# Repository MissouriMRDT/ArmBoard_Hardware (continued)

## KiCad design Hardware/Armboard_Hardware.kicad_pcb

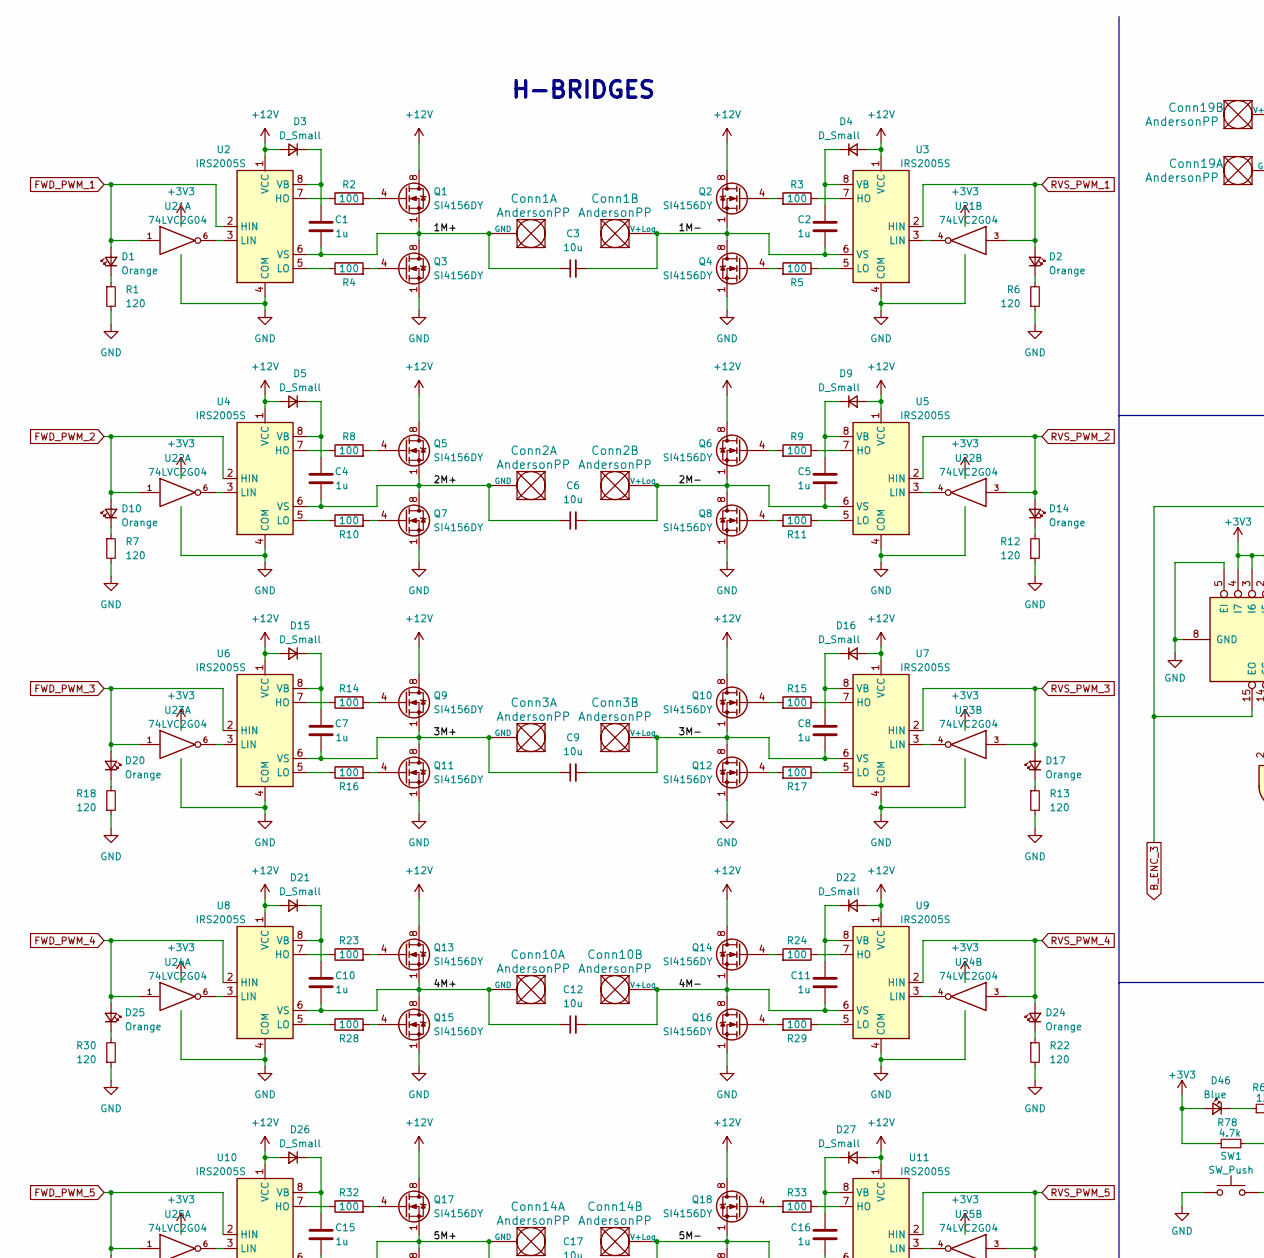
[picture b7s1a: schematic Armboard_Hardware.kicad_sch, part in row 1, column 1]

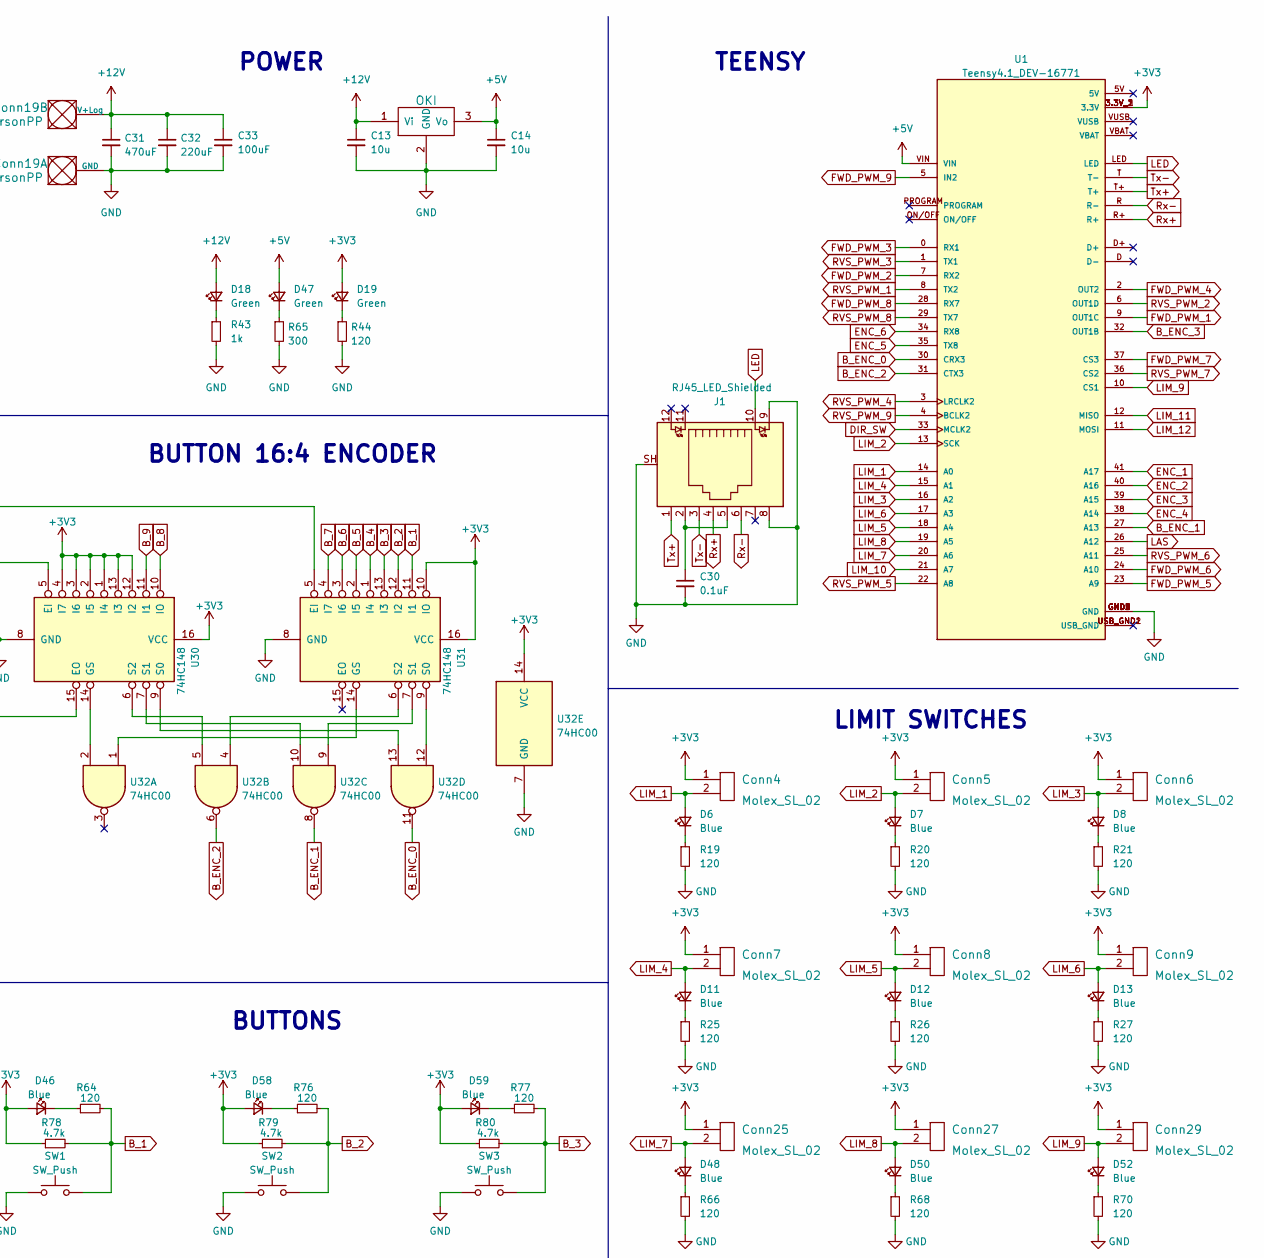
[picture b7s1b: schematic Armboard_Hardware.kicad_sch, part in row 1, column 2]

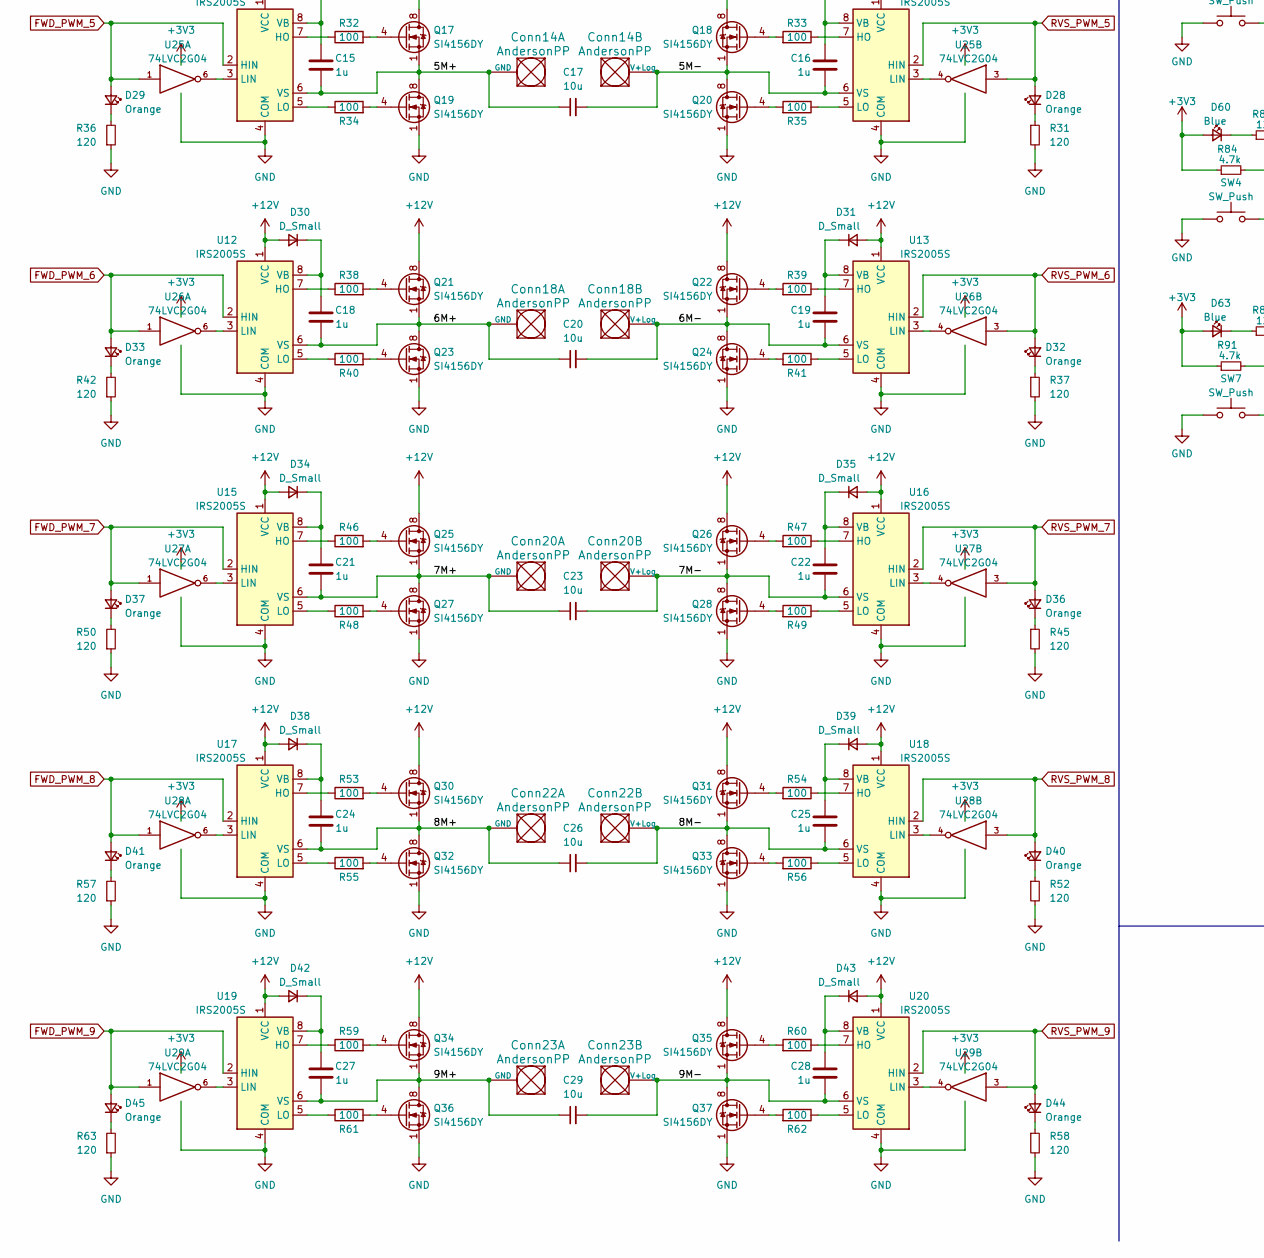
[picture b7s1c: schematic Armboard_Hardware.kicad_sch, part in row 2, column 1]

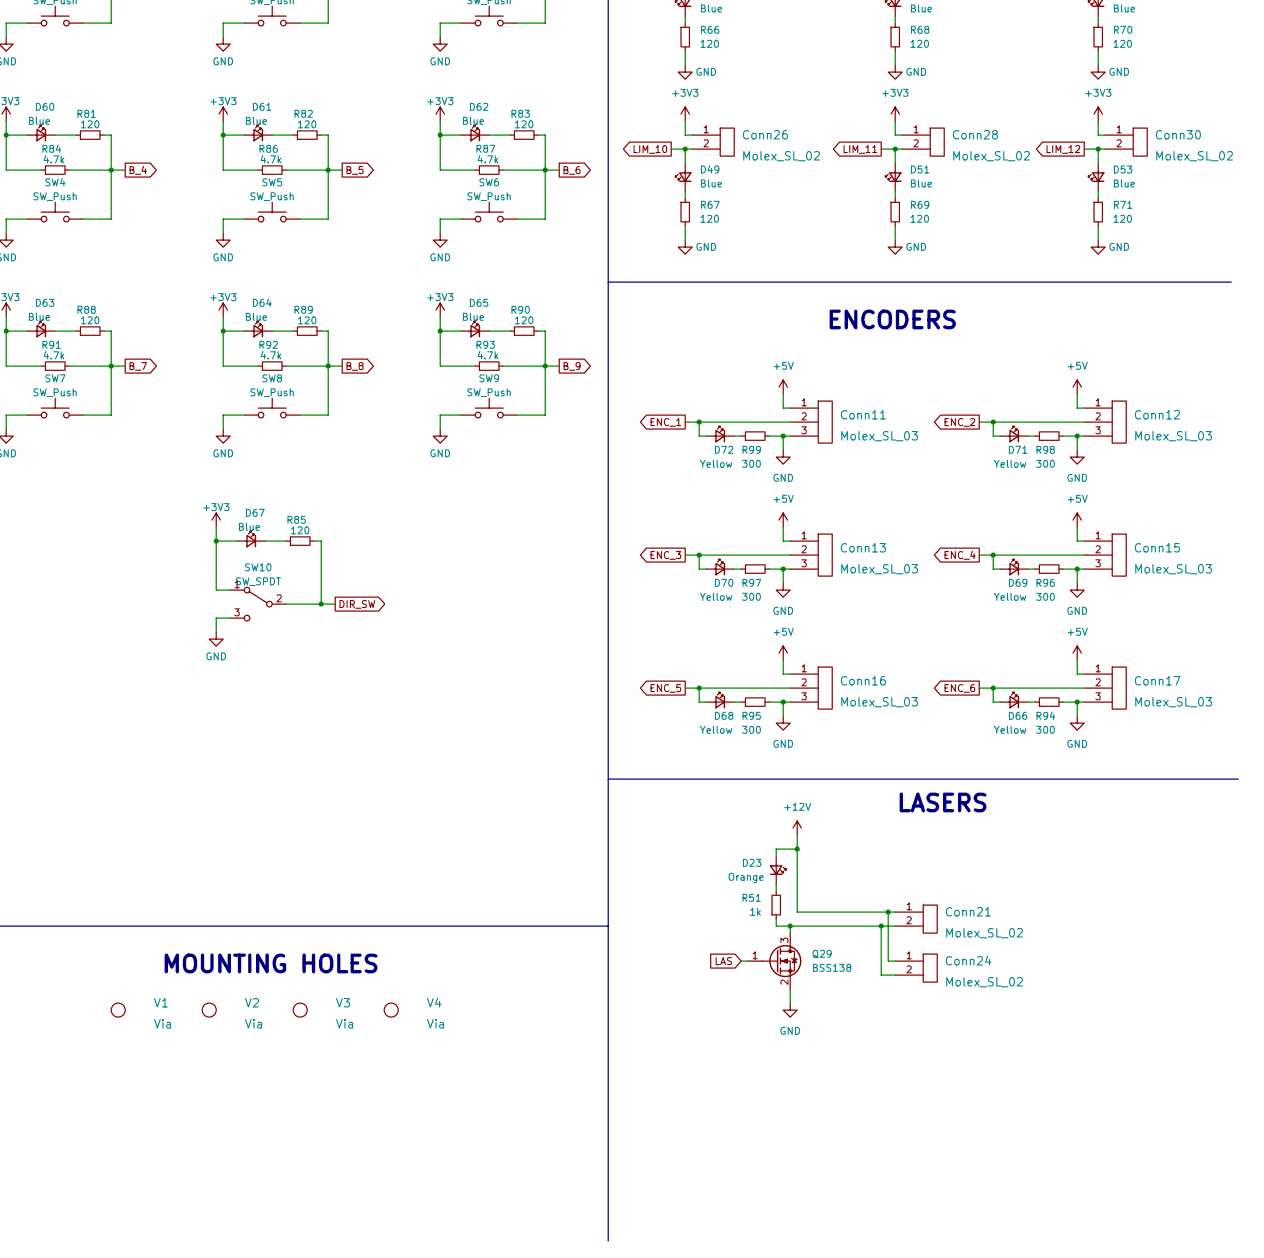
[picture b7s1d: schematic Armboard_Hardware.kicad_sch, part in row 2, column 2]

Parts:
C1, C2, C4, C5, C7, C8, C10, C11, C15, C16, C18, C19, C21, C22, C24, C25, C27, C28: 1u; C_0603_1608Metric
C3, C6, C9, C12, C13, C14, C17, C20, C23, C26, C29: 10u; C_0603_1608Metric
C30: 0.1uF; C_0603_1608Metric
C31: 470uF; CP_Radial_D10.0mm_P2.50mm
C32: 220uF; CP_Radial_D6.3mm_P2.50mm
C33: 100uF; CP_Radial_D6.3mm_P2.50mm
Conn1, Conn2, Conn3, Conn10, Conn14, Conn18, Conn19, Conn20, Conn22, Conn23: AndersonPP; Square_Anderson_2_H_Side_By_Side
Conn4, Conn5, Conn6, Conn7, Conn8, Conn9, Conn21, Conn24, Conn25, Conn26, Conn27, Conn28, Conn29, Conn30: Molex_SL_02; Molex_SL_171971-0002_1x02_P2.54mm_Vertical
Conn11, Conn12, Conn13, Conn15, Conn16, Conn17: Molex_SL_03; Molex_SL_171971-0003_1x03_P2.54mm_Vertical
D1, D2, D10, D14, D17, D20, D23, D24, D25, D28, D29, D32, D33, D36, D37, D40, D41, D44, D45: Orange; LED_0603_1608Metric_Pad1.05x0.95mm_HandSolder
D3, D4, D5, D9, D15, D16, D21, D22, D26, D27, D30, D31, D34, D35, D38, D39, D42, D43: D_Small; LED_0603_1608Metric_Pad1.05x0.95mm_HandSolder
D6, D7, D8, D11, D12, D13, D46, D48, D49, D50, D51, D52, D53, D58, D59, D60, D61, D62, D63, D64, D65, D67: Blue; LED_0603_1608Metric_Pad1.05x0.95mm_HandSolder
D18, D19, D47: Green; LED_0603_1608Metric_Pad1.05x0.95mm_HandSolder
D66, D68, D69, D70, D71, D72: Yellow; LED_0603_1608Metric_Pad1.05x0.95mm_HandSolder
J1: RJ45_LED_Shielded; RJ45_Teensy
Q1, Q2, Q3, Q4, Q5, Q6, Q7, Q8, Q9, Q10, Q11, Q12, Q13, Q14, Q15, Q16, Q17, Q18, Q19, Q20, Q21, Q22, Q23, Q24, Q25, Q26, Q27, Q28, Q30, Q31, Q32, Q33, Q34, Q35, Q36, Q37: SI4156DY; SOIC-8_3.9x4.9mm_P1.27mm
Q29: BSS138; SOT-23
R1, R6, R7, R12, R13, R18, R19, R20, R21, R22, R25, R26, R27, R30, R31, R36, R37, R42, R44, R45, R50, R52, R57, R58, R63, R64, R66, R67, R68, R69, R70, R71, R76, R77, R81, R82, R83, R85, R88, R89, R90: 120; R_0603_1608Metric_Pad0.98x0.95mm_HandSolder
R2, R3, R4, R5, R8, R9, R10, R11, R14, R15, R16, R17, R23, R24, R28, R29, R32, R33, R34, R35, R38, R39, R40, R41, R46, R47, R48, R49, R53, R54, R55, R56, R59, R60, R61, R62: 100; R_0603_1608Metric_Pad0.98x0.95mm_HandSolder
R43, R51: 1k; R_0603_1608Metric_Pad0.98x0.95mm_HandSolder
R65, R94, R95, R96, R97, R98, R99: 300; R_0603_1608Metric_Pad0.98x0.95mm_HandSolder
R78, R79, R80, R84, R86, R87, R91, R92, R93: 4.7k; R_0603_1608Metric_Pad0.98x0.95mm_HandSolder
SW1, SW2, SW3, SW4, SW5, SW6, SW7, SW8, SW9: SW_Push; SW_SPST_TL3305A
SW10: SW_SPDT; SW_Slide_1P2T_CK_OS102011MS2Q
U1: Teensy4.1_DEV-16771; Teensy_4_1_Ethernet; PARTREV 4.1
U2, U3, U4, U5, U6, U7, U8, U9, U10, U11, U12, U13, U15, U16, U17, U18, U19, U20: IRS2005S; SOIC-8_3.9x4.9mm_P1.27mm
U14: OKI; OKI_Horizontal
U21, U22, U23, U24, U25, U26, U27, U28, U29: 74LVC2G04; SOT-23-6_Handsoldering
U30, U31: 74HC148; SOIC-16_4.55x10.3mm_P1.27mm
U32: 74HC00; SO-14_5.3x10.2mm_P1.27mm
V1, V2, V3, V4: Via; 4_40_Hole_Corner

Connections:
+3V3: Conn4.1, Conn5.1, Conn6.1, Conn7.1, Conn8.1, Conn9.1, Conn25.1, Conn26.1, Conn27.1, Conn28.1, Conn29.1, Conn30.1, D19.2 (A), D46.2 (A), D58.2 (A), D59.2 (A), D60.2 (A), D61.2 (A), D62.2 (A), D63.2 (A), D64.2 (A), D65.2 (A), D67.2 (A), R78.1, R79.1, R80.1, R84.1, R86.1, R87.1, R91.1, R92.1, R93.1, SW10.1 (A), U1.3.3V_1 (3.3V), U1.3.3V_2 (3.3V), U1.3.3V_3 (3.3V), U21.5 (VCC), U22.5 (VCC), U23.5 (VCC), U24.5 (VCC), U25.5 (VCC), U26.5 (VCC), U27.5 (VCC), U28.5 (VCC), U29.5 (VCC), U30.1 (I4), U30.2 (I5), U30.3 (I6), U30.4 (I7), U30.12 (I2), U30.13 (I3), U30.16 (VCC), U31.10 (IO), U31.16 (VCC), U32.14 (VCC)
+5V: C14.1, Conn11.1, Conn12.1, Conn13.1, Conn15.1, Conn16.1, Conn17.1, D47.2 (A), U1.VIN, U14.3 (Vo)
+12V: C13.1, C31.1, C32.1, C33.1, Conn19.2 (V+Log), Conn21.1, Conn24.1, D3.2 (A), D4.2 (A), D5.2 (A), D9.2 (A), D15.2 (A), D16.2 (A), D18.2 (A), D21.2 (A), D22.2 (A), D23.2 (A), D26.2 (A), D27.2 (A), D30.2 (A), D31.2 (A), D34.2 (A), D35.2 (A), D38.2 (A), D39.2 (A), D42.2 (A), D43.2 (A), Q1.5 (D), Q1.6 (D), Q1.7 (D), Q1.8 (D), Q2.5 (D), Q2.6 (D), Q2.7 (D), Q2.8 (D), Q5.5 (D), Q5.6 (D), Q5.7 (D), Q5.8 (D), Q6.5 (D), Q6.6 (D), Q6.7 (D), Q6.8 (D), Q9.5 (D), Q9.6 (D), Q9.7 (D), Q9.8 (D), Q10.5 (D), Q10.6 (D), Q10.7 (D), Q10.8 (D), Q13.5 (D), Q13.6 (D), Q13.7 (D), Q13.8 (D), Q14.5 (D), Q14.6 (D), Q14.7 (D), Q14.8 (D), Q17.5 (D), Q17.6 (D), Q17.7 (D), Q17.8 (D), Q18.5 (D), Q18.6 (D), Q18.7 (D), Q18.8 (D), Q21.5 (D), Q21.6 (D), Q21.7 (D), Q21.8 (D), Q22.5 (D), Q22.6 (D), Q22.7 (D), Q22.8 (D), Q25.5 (D), Q25.6 (D), Q25.7 (D), Q25.8 (D), Q26.5 (D), Q26.6 (D), Q26.7 (D), Q26.8 (D), Q30.5 (D), Q30.6 (D), Q30.7 (D), Q30.8 (D), Q31.5 (D), Q31.6 (D), Q31.7 (D), Q31.8 (D), Q34.5 (D), Q34.6 (D), Q34.7 (D), Q34.8 (D), Q35.5 (D), Q35.6 (D), Q35.7 (D), Q35.8 (D), U2.1 (VCC), U3.1 (VCC), U4.1 (VCC), U5.1 (VCC), U6.1 (VCC), U7.1 (VCC), U8.1 (VCC), U9.1 (VCC), U10.1 (VCC), U11.1 (VCC), U12.1 (VCC), U13.1 (VCC), U14.1 (Vi), U15.1 (VCC), U16.1 (VCC), U17.1 (VCC), U18.1 (VCC), U19.1 (VCC), U20.1 (VCC)
/1M+: C1.2, C3.1, Conn1.1 (GND), Q1.1 (S), Q1.2 (S), Q1.3 (S), Q3.5 (D), Q3.6 (D), Q3.7 (D), Q3.8 (D), U2.6 (VS)
/1M-: C2.2, C3.2, Conn1.2 (V+Log), Q2.1 (S), Q2.2 (S), Q2.3 (S), Q4.5 (D), Q4.6 (D), Q4.7 (D), Q4.8 (D), U3.6 (VS)
/2M+: C4.2, C6.1, Conn2.1 (GND), Q5.1 (S), Q5.2 (S), Q5.3 (S), Q7.5 (D), Q7.6 (D), Q7.7 (D), Q7.8 (D), U4.6 (VS)
/2M-: C5.2, C6.2, Conn2.2 (V+Log), Q6.1 (S), Q6.2 (S), Q6.3 (S), Q8.5 (D), Q8.6 (D), Q8.7 (D), Q8.8 (D), U5.6 (VS)
/3M+: C7.2, C9.1, Conn3.1 (GND), Q9.1 (S), Q9.2 (S), Q9.3 (S), Q11.5 (D), Q11.6 (D), Q11.7 (D), Q11.8 (D), U6.6 (VS)
/3M-: C8.2, C9.2, Conn3.2 (V+Log), Q10.1 (S), Q10.2 (S), Q10.3 (S), Q12.5 (D), Q12.6 (D), Q12.7 (D), Q12.8 (D), U7.6 (VS)
/4M+: C10.2, C12.1, Conn10.1 (GND), Q13.1 (S), Q13.2 (S), Q13.3 (S), Q15.5 (D), Q15.6 (D), Q15.7 (D), Q15.8 (D), U8.6 (VS)
/4M-: C11.2, C12.2, Conn10.2 (V+Log), Q14.1 (S), Q14.2 (S), Q14.3 (S), Q16.5 (D), Q16.6 (D), Q16.7 (D), Q16.8 (D), U9.6 (VS)
/5M+: C15.2, C17.1, Conn14.1 (GND), Q17.1 (S), Q17.2 (S), Q17.3 (S), Q19.5 (D), Q19.6 (D), Q19.7 (D), Q19.8 (D), U10.6 (VS)
/5M-: C16.2, C17.2, Conn14.2 (V+Log), Q18.1 (S), Q18.2 (S), Q18.3 (S), Q20.5 (D), Q20.6 (D), Q20.7 (D), Q20.8 (D), U11.6 (VS)
/6M+: C18.2, C20.1, Conn18.1 (GND), Q21.1 (S), Q21.2 (S), Q21.3 (S), Q23.5 (D), Q23.6 (D), Q23.7 (D), Q23.8 (D), U12.6 (VS)
/6M-: C19.2, C20.2, Conn18.2 (V+Log), Q22.1 (S), Q22.2 (S), Q22.3 (S), Q24.5 (D), Q24.6 (D), Q24.7 (D), Q24.8 (D), U13.6 (VS)
/7M+: C21.2, C23.1, Conn20.1 (GND), Q25.1 (S), Q25.2 (S), Q25.3 (S), Q27.5 (D), Q27.6 (D), Q27.7 (D), Q27.8 (D), U15.6 (VS)
/7M-: C22.2, C23.2, Conn20.2 (V+Log), Q26.1 (S), Q26.2 (S), Q26.3 (S), Q28.5 (D), Q28.6 (D), Q28.7 (D), Q28.8 (D), U16.6 (VS)
/8M+: C24.2, C26.1, Conn22.1 (GND), Q30.1 (S), Q30.2 (S), Q30.3 (S), Q32.5 (D), Q32.6 (D), Q32.7 (D), Q32.8 (D), U17.6 (VS)
/8M-: C25.2, C26.2, Conn22.2 (V+Log), Q31.1 (S), Q31.2 (S), Q31.3 (S), Q33.5 (D), Q33.6 (D), Q33.7 (D), Q33.8 (D), U18.6 (VS)
/9M+: C27.2, C29.1, Conn23.1 (GND), Q34.1 (S), Q34.2 (S), Q34.3 (S), Q36.5 (D), Q36.6 (D), Q36.7 (D), Q36.8 (D), U19.6 (VS)
/9M-: C28.2, C29.2, Conn23.2 (V+Log), Q35.1 (S), Q35.2 (S), Q35.3 (S), Q37.5 (D), Q37.6 (D), Q37.7 (D), Q37.8 (D), U20.6 (VS)
B_1: R64.2, R78.2, SW1.2, U31.11 (I1)
B_2: R76.2, R79.2, SW2.2, U31.12 (I2)
B_3: R77.2, R80.2, SW3.2, U31.13 (I3)
B_4: R81.2, R84.2, SW4.2, U31.1 (I4)
B_5: R82.2, R86.2, SW5.2, U31.2 (I5)
B_6: R83.2, R87.2, SW6.2, U31.3 (I6)
B_7: R88.2, R91.2, SW7.2, U31.4 (I7)
B_8: R89.2, R92.2, SW8.2, U30.10 (IO)
B_9: R90.2, R93.2, SW9.2, U30.11 (I1)
B_ENC_0: U1.30 (CRX3), U32.11
B_ENC_1: U1.27 (A13), U32.8
B_ENC_2: U1.31 (CTX3), U32.6
B_ENC_3: U1.32 (OUT1B), U30.15 (EO), U31.5 (EI)
DIR_SW: R85.2, SW10.2 (B), U1.33 (MCLK2)
ENC_1: Conn11.2, D72.2 (A), U1.41 (A17)
ENC_2: Conn12.2, D71.2 (A), U1.40 (A16)
ENC_3: Conn13.2, D70.2 (A), U1.39 (A15)
ENC_4: Conn15.2, D69.2 (A), U1.38 (A14)
ENC_5: Conn16.2, D68.2 (A), U1.35 (TX8)
ENC_6: Conn17.2, D66.2 (A), U1.34 (RX8)
FWD_PWM_1: D1.2 (A), U1.9 (OUT1C), U2.2 (HIN), U21.1
FWD_PWM_2: D10.2 (A), U1.7 (RX2), U4.2 (HIN), U22.1
FWD_PWM_3: D20.2 (A), U1.0 (RX1), U6.2 (HIN), U23.1
FWD_PWM_4: D25.2 (A), U1.2 (OUT2), U8.2 (HIN), U24.1
FWD_PWM_5: D29.2 (A), U1.23 (A9), U10.2 (HIN), U25.1
FWD_PWM_6: D33.2 (A), U1.24 (A10), U12.2 (HIN), U26.1
FWD_PWM_7: D37.2 (A), U1.37 (CS3), U15.2 (HIN), U27.1
FWD_PWM_8: D41.2 (A), U1.28 (RX7), U17.2 (HIN), U28.1
FWD_PWM_9: D45.2 (A), U1.5 (IN2), U19.2 (HIN), U29.1
GND: C13.2, C14.2, C30.2, C31.2, C32.2, C33.2, Conn11.3, Conn12.3, Conn13.3, Conn15.3, Conn16.3, Conn17.3, Conn19.1 (GND), J1.8, J1.9, J1.SH, Q3.1 (S), Q3.2 (S), Q3.3 (S), Q4.1 (S), Q4.2 (S), Q4.3 (S), Q7.1 (S), Q7.2 (S), Q7.3 (S), Q8.1 (S), Q8.2 (S), Q8.3 (S), Q11.1 (S), Q11.2 (S), Q11.3 (S), Q12.1 (S), Q12.2 (S), Q12.3 (S), Q15.1 (S), Q15.2 (S), Q15.3 (S), Q16.1 (S), Q16.2 (S), Q16.3 (S), Q19.1 (S), Q19.2 (S), Q19.3 (S), Q20.1 (S), Q20.2 (S), Q20.3 (S), Q23.1 (S), Q23.2 (S), Q23.3 (S), Q24.1 (S), Q24.2 (S), Q24.3 (S), Q27.1 (S), Q27.2 (S), Q27.3 (S), Q28.1 (S), Q28.2 (S), Q28.3 (S), Q29.2 (S), Q32.1 (S), Q32.2 (S), Q32.3 (S), Q33.1 (S), Q33.2 (S), Q33.3 (S), Q36.1 (S), Q36.2 (S), Q36.3 (S), Q37.1 (S), Q37.2 (S), Q37.3 (S), R1.2, R6.1, R7.2, R12.1, R13.2, R18.1, R19.2, R20.2, R21.2, R22.2, R25.2, R26.2, R27.2, R30.1, R31.2, R36.1, R37.2, R42.1, R43.2, R44.2, R45.2, R50.1, R52.2, R57.1, R58.2, R63.1, R65.2, R66.2, R67.2, R68.2, R69.2, R70.2, R71.2, R94.2, R95.2, R96.2, R97.2, R98.2, R99.2, SW1.1, SW2.1, SW3.1, SW4.1, SW5.1, SW6.1, SW7.1, SW8.1, SW9.1, SW10.3 (C), U1.GND1 (GND), U1.GND2 (GND), U1.GND3 (GND), U1.GND4 (GND), U1.GND5 (GND), U2.4 (COM), U3.4 (COM), U4.4 (COM), U5.4 (COM), U6.4 (COM), U7.4 (COM), U8.4 (COM), U9.4 (COM), U10.4 (COM), U11.4 (COM), U12.4 (COM), U13.4 (COM), U14.2 (GND), U15.4 (COM), U16.4 (COM), U17.4 (COM), U18.4 (COM), U19.4 (COM), U20.4 (COM), U21.2 (GND), U22.2 (GND), U23.2 (GND), U24.2 (GND), U25.2 (GND), U26.2 (GND), U27.2 (GND), U28.2 (GND), U29.2 (GND), U30.5 (EI), U30.8 (GND), U31.8 (GND), U32.7 (GND)
LAS: Q29.1 (G), U1.26 (A12)
LED: J1.10, U1.LED
LIM_1: Conn4.2, D6.2 (A), U1.14 (A0)
LIM_2: Conn5.2, D7.2 (A), U1.13 (SCK)
LIM_3: Conn6.2, D8.2 (A), U1.16 (A2)
LIM_4: Conn7.2, D11.2 (A), U1.15 (A1)
LIM_5: Conn8.2, D12.2 (A), U1.18 (A4)
LIM_6: Conn9.2, D13.2 (A), U1.17 (A3)
LIM_7: Conn25.2, D48.2 (A), U1.20 (A6)
LIM_8: Conn27.2, D50.2 (A), U1.19 (A5)
LIM_9: Conn29.2, D52.2 (A), U1.10 (CS1)
LIM_10: Conn26.2, D49.2 (A), U1.21 (A7)
LIM_11: Conn28.2, D51.2 (A), U1.12 (MISO)
LIM_12: Conn30.2, D53.2 (A), U1.11 (MOSI)
unnamed: C1.1, D3.1 (K), U2.8 (VB)
unnamed: C2.1, D4.1 (K), U3.8 (VB)
unnamed: C4.1, D5.1 (K), U4.8 (VB)
unnamed: C5.1, D9.1 (K), U5.8 (VB)
unnamed: C7.1, D15.1 (K), U6.8 (VB)
unnamed: C8.1, D16.1 (K), U7.8 (VB)
unnamed: C10.1, D21.1 (K), U8.8 (VB)
unnamed: C11.1, D22.1 (K), U9.8 (VB)
unnamed: C15.1, D26.1 (K), U10.8 (VB)
unnamed: C16.1, D27.1 (K), U11.8 (VB)
unnamed: C18.1, D30.1 (K), U12.8 (VB)
unnamed: C19.1, D31.1 (K), U13.8 (VB)
unnamed: C21.1, D34.1 (K), U15.8 (VB)
unnamed: C22.1, D35.1 (K), U16.8 (VB)
unnamed: C24.1, D38.1 (K), U17.8 (VB)
unnamed: C25.1, D39.1 (K), U18.8 (VB)
unnamed: C27.1, D42.1 (K), U19.8 (VB)
unnamed: C28.1, D43.1 (K), U20.8 (VB)
unnamed: C30.1, J1.2, J1.5
unnamed: Conn21.2, Conn24.2, Q29.3 (D), R51.1
unnamed: D1.1 (K), R1.1
unnamed: D2.1 (K), R6.2
unnamed: D6.1 (K), R19.1
unnamed: D7.1 (K), R20.1
unnamed: D8.1 (K), R21.1
unnamed: D10.1 (K), R7.1
unnamed: D11.1 (K), R25.1
unnamed: D12.1 (K), R26.1
unnamed: D13.1 (K), R27.1
unnamed: D14.1 (K), R12.2
unnamed: D17.1 (K), R13.1
unnamed: D18.1 (K), R43.1
unnamed: D19.1 (K), R44.1
unnamed: D20.1 (K), R18.2
unnamed: D23.1 (K), R51.2
unnamed: D24.1 (K), R22.1
unnamed: D25.1 (K), R30.2
unnamed: D28.1 (K), R31.1
unnamed: D29.1 (K), R36.2
unnamed: D32.1 (K), R37.1
unnamed: D33.1 (K), R42.2
unnamed: D36.1 (K), R45.1
unnamed: D37.1 (K), R50.2
unnamed: D40.1 (K), R52.1
unnamed: D41.1 (K), R57.2
unnamed: D44.1 (K), R58.1
unnamed: D45.1 (K), R63.2
unnamed: D46.1 (K), R64.1
unnamed: D47.1 (K), R65.1
unnamed: D48.1 (K), R66.1
unnamed: D49.1 (K), R67.1
unnamed: D50.1 (K), R68.1
unnamed: D51.1 (K), R69.1
unnamed: D52.1 (K), R70.1
unnamed: D53.1 (K), R71.1
unnamed: D58.1 (K), R76.1
unnamed: D59.1 (K), R77.1
unnamed: D60.1 (K), R81.1
unnamed: D61.1 (K), R82.1
unnamed: D62.1 (K), R83.1
unnamed: D63.1 (K), R88.1
unnamed: D64.1 (K), R89.1
unnamed: D65.1 (K), R90.1
unnamed: D66.1 (K), R94.1
unnamed: D67.1 (K), R85.1
unnamed: D68.1 (K), R95.1
unnamed: D69.1 (K), R96.1
unnamed: D70.1 (K), R97.1
unnamed: D71.1 (K), R98.1
unnamed: D72.1 (K), R99.1
unnamed: Q1.4 (G), R2.2
unnamed: Q2.4 (G), R3.2
unnamed: Q3.4 (G), R4.2
unnamed: Q4.4 (G), R5.2
unnamed: Q5.4 (G), R8.2
unnamed: Q6.4 (G), R9.2
unnamed: Q7.4 (G), R10.2
unnamed: Q8.4 (G), R11.2
unnamed: Q9.4 (G), R14.2
unnamed: Q10.4 (G), R15.2
unnamed: Q11.4 (G), R16.2
unnamed: Q12.4 (G), R17.2
unnamed: Q13.4 (G), R23.2
unnamed: Q14.4 (G), R24.2
unnamed: Q15.4 (G), R28.2
unnamed: Q16.4 (G), R29.2
unnamed: Q17.4 (G), R32.2
unnamed: Q18.4 (G), R33.2
unnamed: Q19.4 (G), R34.2
unnamed: Q20.4 (G), R35.2
unnamed: Q21.4 (G), R38.2
unnamed: Q22.4 (G), R39.2
unnamed: Q23.4 (G), R40.2
unnamed: Q24.4 (G), R41.2
unnamed: Q25.4 (G), R46.2
unnamed: Q26.4 (G), R47.2
unnamed: Q27.4 (G), R48.2
unnamed: Q28.4 (G), R49.2
unnamed: Q30.4 (G), R53.2
unnamed: Q31.4 (G), R54.2
unnamed: Q32.4 (G), R55.2
unnamed: Q33.4 (G), R56.2
unnamed: Q34.4 (G), R59.2
unnamed: Q35.4 (G), R60.2
unnamed: Q36.4 (G), R61.2
unnamed: Q37.4 (G), R62.2
unnamed: R2.1, U2.7 (HO)
unnamed: R3.1, U3.7 (HO)
unnamed: R4.1, U2.5 (LO)
unnamed: R5.1, U3.5 (LO)
unnamed: R8.1, U4.7 (HO)
unnamed: R9.1, U5.7 (HO)
unnamed: R10.1, U4.5 (LO)
unnamed: R11.1, U5.5 (LO)
unnamed: R14.1, U6.7 (HO)
unnamed: R15.1, U7.7 (HO)
unnamed: R16.1, U6.5 (LO)
unnamed: R17.1, U7.5 (LO)
unnamed: R23.1, U8.7 (HO)
unnamed: R24.1, U9.7 (HO)
unnamed: R28.1, U8.5 (LO)
unnamed: R29.1, U9.5 (LO)
unnamed: R32.1, U10.7 (HO)
unnamed: R33.1, U11.7 (HO)
unnamed: R34.1, U10.5 (LO)
unnamed: R35.1, U11.5 (LO)
unnamed: R38.1, U12.7 (HO)
unnamed: R39.1, U13.7 (HO)
unnamed: R40.1, U12.5 (LO)
unnamed: R41.1, U13.5 (LO)
unnamed: R46.1, U15.7 (HO)
unnamed: R47.1, U16.7 (HO)
unnamed: R48.1, U15.5 (LO)
unnamed: R49.1, U16.5 (LO)
unnamed: R53.1, U17.7 (HO)
unnamed: R54.1, U18.7 (HO)
unnamed: R55.1, U17.5 (LO)
unnamed: R56.1, U18.5 (LO)
unnamed: R59.1, U19.7 (HO)
unnamed: R60.1, U20.7 (HO)
unnamed: R61.1, U19.5 (LO)
unnamed: R62.1, U20.5 (LO)
unnamed: U2.3 (LIN), U21.6
unnamed: U10.3 (LIN), U25.6
unnamed: U11.3 (LIN), U25.4
unnamed: U12.3 (LIN), U26.6
unnamed: U13.3 (LIN), U26.4
unnamed: U15.3 (LIN), U27.6
unnamed: U16.3 (LIN), U27.4
unnamed: U17.3 (LIN), U28.6
unnamed: U18.3 (LIN), U28.4
unnamed: U19.3 (LIN), U29.6
unnamed: U20.3 (LIN), U29.4
unnamed: U3.3 (LIN), U21.4
unnamed: U5.3 (LIN), U22.4
unnamed: U4.3 (LIN), U22.6
unnamed: U7.3 (LIN), U23.4
unnamed: U6.3 (LIN), U23.6
unnamed: U9.3 (LIN), U24.4
unnamed: U8.3 (LIN), U24.6
unnamed: U30.6 (S2), U32.5
unnamed: U30.7 (S1), U32.10
unnamed: U30.9 (S0), U32.13
unnamed: U30.14 (GS), U32.2
unnamed: U31.6 (S2), U32.4
unnamed: U31.7 (S1), U32.9
unnamed: U31.9 (S0), U32.12
unnamed: U31.14 (GS), U32.1
RVS_PWM_1: D2.2 (A), U1.8 (TX2), U3.2 (HIN), U21.3
RVS_PWM_2: D14.2 (A), U1.6 (OUT1D), U5.2 (HIN), U22.3
RVS_PWM_3: D17.2 (A), U1.1 (TX1), U7.2 (HIN), U23.3
RVS_PWM_4: D24.2 (A), U1.3 (LRCLK2), U9.2 (HIN), U24.3
RVS_PWM_5: D28.2 (A), U1.22 (A8), U11.2 (HIN), U25.3
RVS_PWM_6: D32.2 (A), U1.25 (A11), U13.2 (HIN), U26.3
RVS_PWM_7: D36.2 (A), U1.36 (CS2), U16.2 (HIN), U27.3
RVS_PWM_8: D40.2 (A), U1.29 (TX7), U18.2 (HIN), U28.3
RVS_PWM_9: D44.2 (A), U1.4 (BCLK2), U20.2 (HIN), U29.3
Rx+: J1.4, U1.R+
Rx-: J1.6, U1.R (R-), U1.R-
Tx+: J1.1, U1.T+
Tx-: J1.3, U1.T (T-), U1.T-

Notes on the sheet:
LIMIT SWITCHES
ENCODERS
POWER
BUTTONS
MOUNTING HOLES
BUTTON 16:4 ENCODER
LASERS
H-BRIDGES
TEENSY

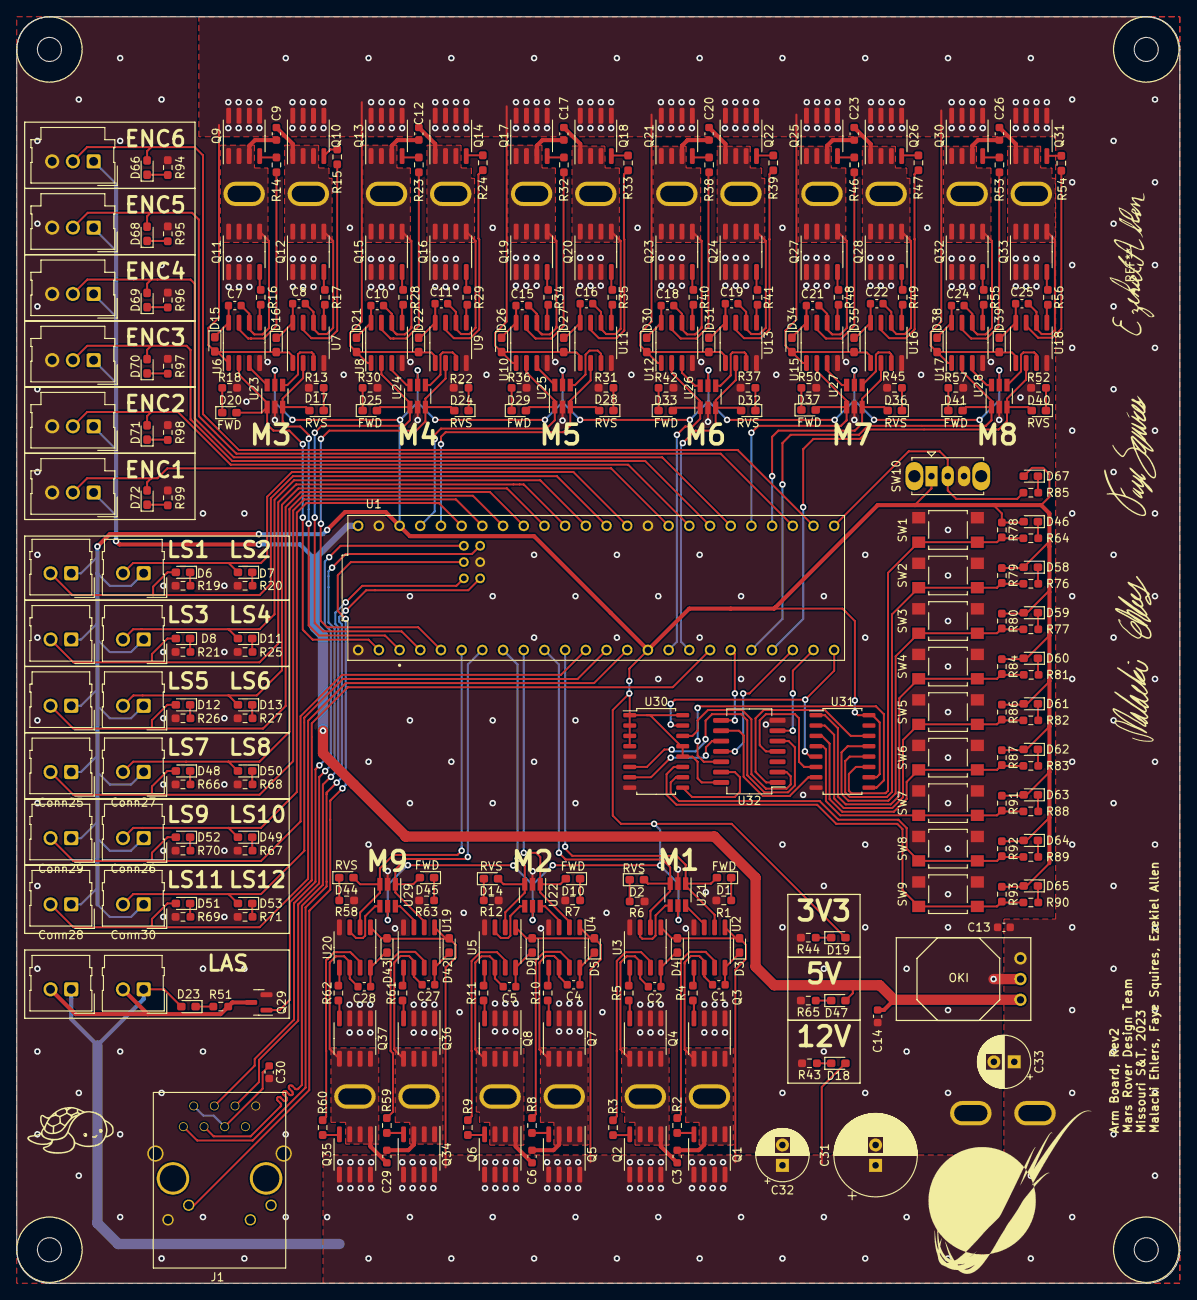
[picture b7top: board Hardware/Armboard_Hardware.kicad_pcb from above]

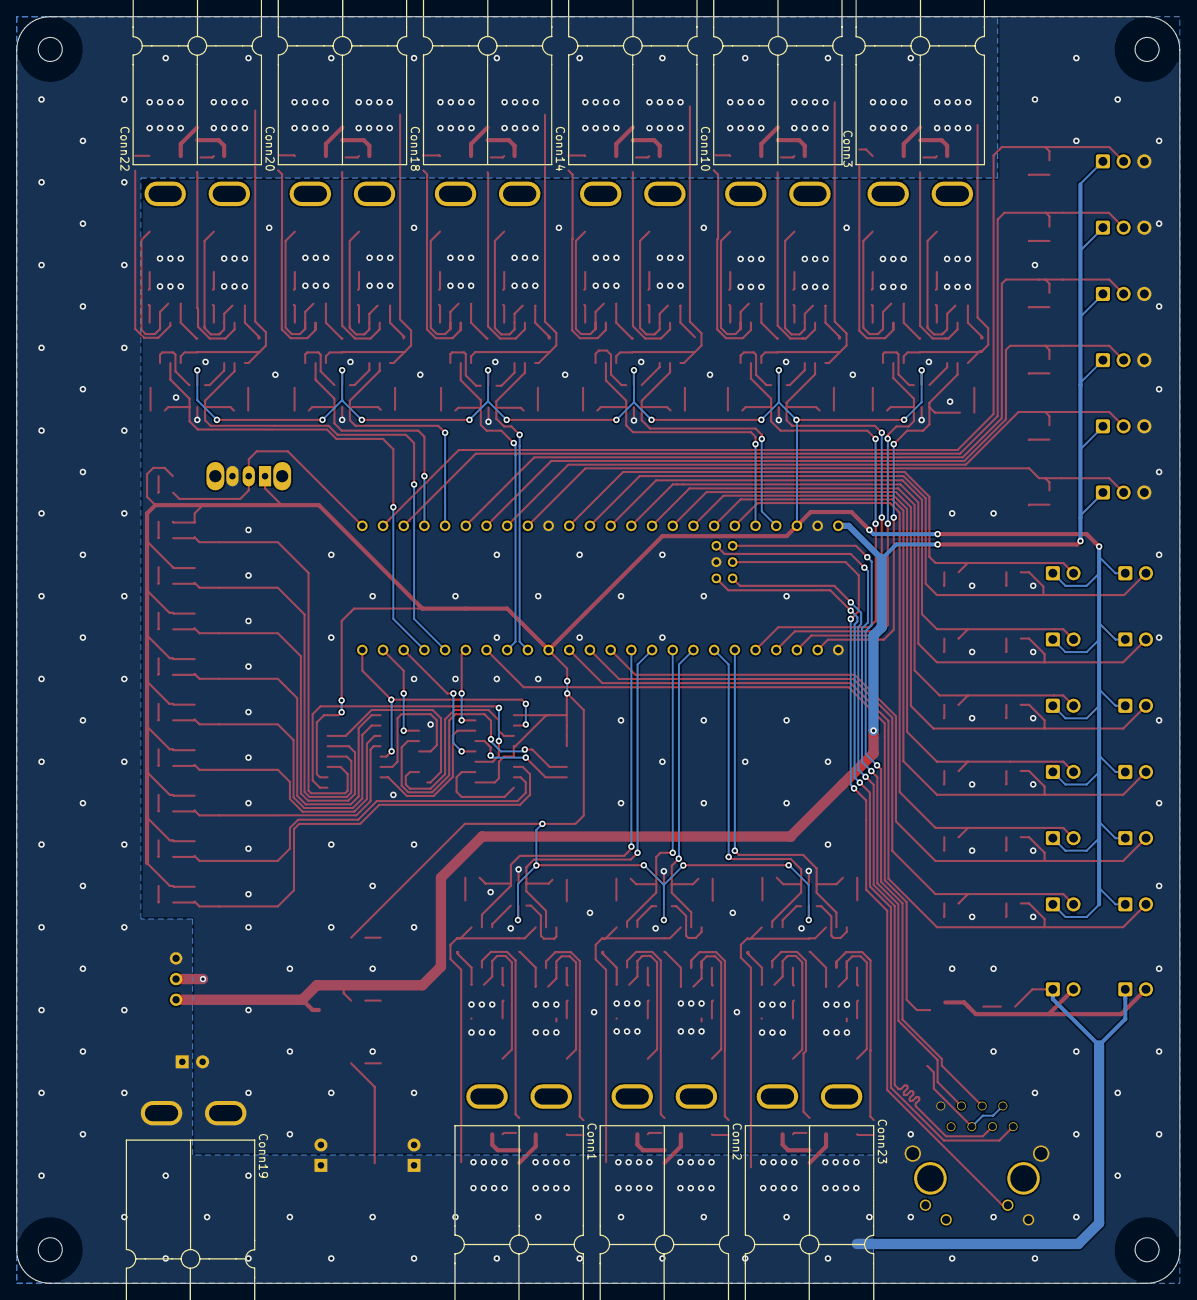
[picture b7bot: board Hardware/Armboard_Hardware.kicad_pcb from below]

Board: 2 copper layers, 142.7 x 155.4 mm, 310 parts (9 on the bottom side), 246 nets.

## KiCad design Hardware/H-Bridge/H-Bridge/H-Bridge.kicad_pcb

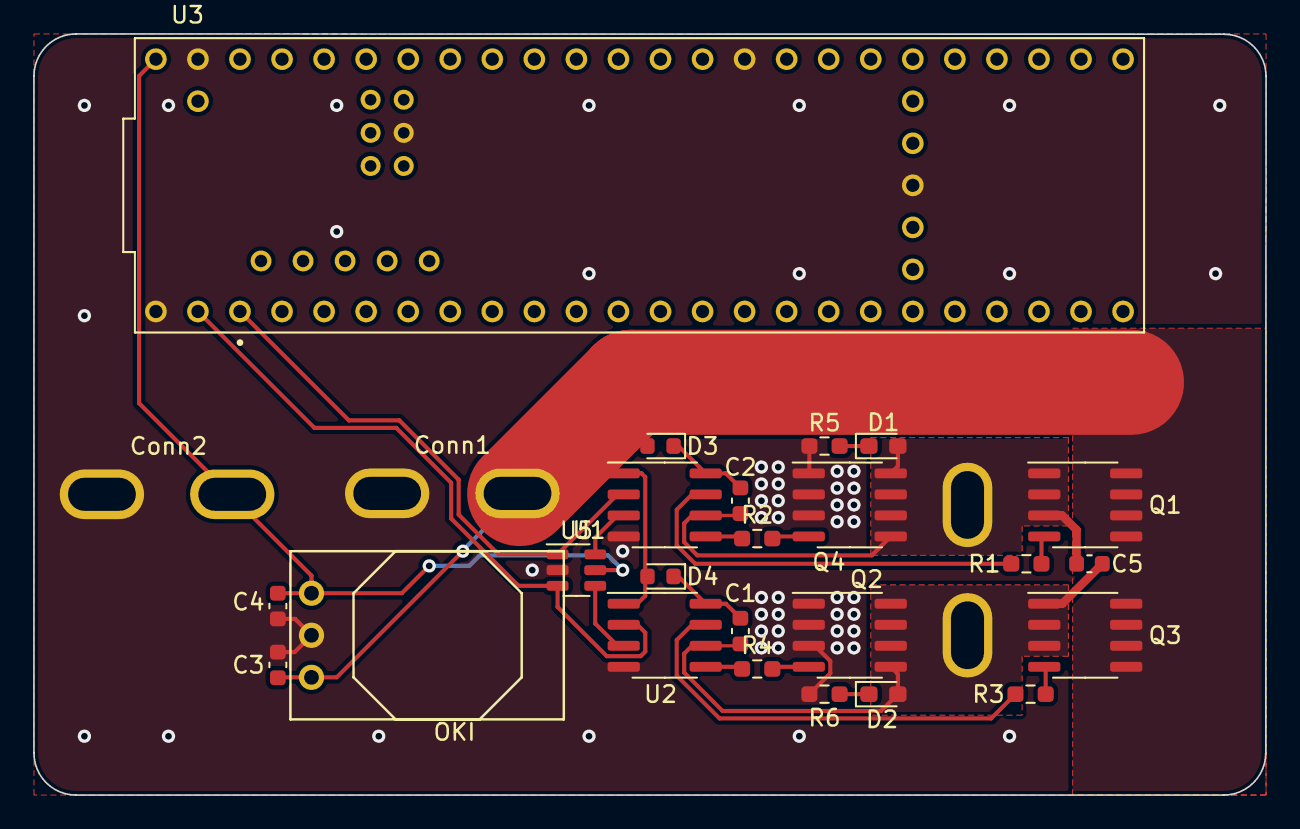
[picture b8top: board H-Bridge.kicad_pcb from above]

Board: 2 copper layers, 74.4 x 46.0 mm, 27 parts (1 on the bottom side), 21 nets.

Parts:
C1, C2: 0.1u; C_0603_1608Metric
C3, C4, C5: 10u; C_0603_1608Metric
Conn1, Conn2, Conn3: AndersonPP; Square_Anderson_2_H_Side_By_Side
D1, D2: Pink; LED_0603_1608Metric_Pad1.05x0.95mm_HandSolder
D3, D4: SD0603S040S0R2; D_0603_1608Metric
Q1, Q2, Q3, Q4: SI4156DY; SOIC-8_3.9x4.9mm_P1.27mm
R1, R2, R3, R4: 100; R_0603_1608Metric_Pad0.98x0.95mm_HandSolder
R5, R6: 500; R_0603_1608Metric_Pad0.98x0.95mm_HandSolder
U1, U2: IRS2005S; SOIC-8_3.9x4.9mm_P1.27mm
U3: Teensy4.1_DEV-16771; MODULE_DEV-16771
U4: OKI; OKI_Horizontal
U5: 74LVC2G04; SOT-23-6

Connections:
+3V3: C4.1, Conn2.2 (V+Log), U3.VIN, U4.3 (Vo), U5.5 (VCC)
+12V: C3.1, Conn1.2 (V+Log), D3.2 (A), D4.2 (A), Q1.5 (D), Q1.6 (D), Q1.7 (D), Q1.8 (D), Q3.5 (D), Q3.6 (D), Q3.7 (D), Q3.8 (D), U1.1 (VCC), U2.1 (VCC), U4.1 (Vi)
/M+: C2.2, C5.1, Conn3.1 (GND), D1.2 (A), Q1.1 (S), Q1.2 (S), Q1.3 (S), Q4.5 (D), Q4.6 (D), Q4.7 (D), Q4.8 (D), U1.6 (VS)
/M-: C1.2, C5.2, Conn3.2 (V+Log), D2.2 (A), Q2.5 (D), Q2.6 (D), Q2.7 (D), Q2.8 (D), Q3.1 (S), Q3.2 (S), Q3.3 (S), U2.6 (VS)
FWD_PWM: U1.2 (HIN), U3.1 (TX1), U5.1
GND: C3.2, C4.2, Conn1.1 (GND), Conn2.1 (GND), Q2.1 (S), Q2.2 (S), Q2.3 (S), Q4.1 (S), Q4.2 (S), Q4.3 (S), R5.2, R6.2, U1.4 (COM), U2.4 (COM), U3.GND1 (GND), U3.GND2 (GND), U3.GND3 (GND), U3.GND4 (GND), U3.GND5 (GND), U4.2 (GND), U5.2 (GND)
unnamed: C1.1, D4.1 (K), U2.8 (VB)
unnamed: C2.1, D3.1 (K), U1.8 (VB)
unnamed: D1.1 (K), R5.1
unnamed: D2.1 (K), R6.1
unnamed: Q1.4 (G), R1.2
unnamed: Q2.4 (G), R4.2
unnamed: Q3.4 (G), R3.2
unnamed: Q4.4 (G), R2.2
unnamed: R1.1, U1.7 (HO)
unnamed: R2.1, U1.5 (LO)
unnamed: R3.1, U2.7 (HO)
unnamed: R4.1, U2.5 (LO)
unnamed: U1.3 (LIN), U5.6
unnamed: U2.3 (LIN), U5.4
RVS_PWM: U2.2 (HIN), U3.0 (RX1), U5.3
